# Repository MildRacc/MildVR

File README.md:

# MildVR

MildVR is a completely open-source VR headset with Windows, Linux, and macOS support in mind front the get-go. The goal of this project is to move away from the closed ecosystems of major VR companies like Meta. With the Quest lineup, Meta forces users to make accounts and limits PCVR usage to Windows by keeping their runtime proprietary. That means anyone using macOS or Linux is locked out completely. MildVR is different. It will use the open-source Monado runtime, which works across all three major desktop operating systems. It will never require and account, sign-in, or any proprietary software to function. Every part of the project, from the headset hardware, to the controllers, to the source code, will all be open for anyone to study, modify, or improve. My ultimate goal is to create a VR headset that anyone can build, understand, and use freely without being tied to any company, operating system, or proprietary software.

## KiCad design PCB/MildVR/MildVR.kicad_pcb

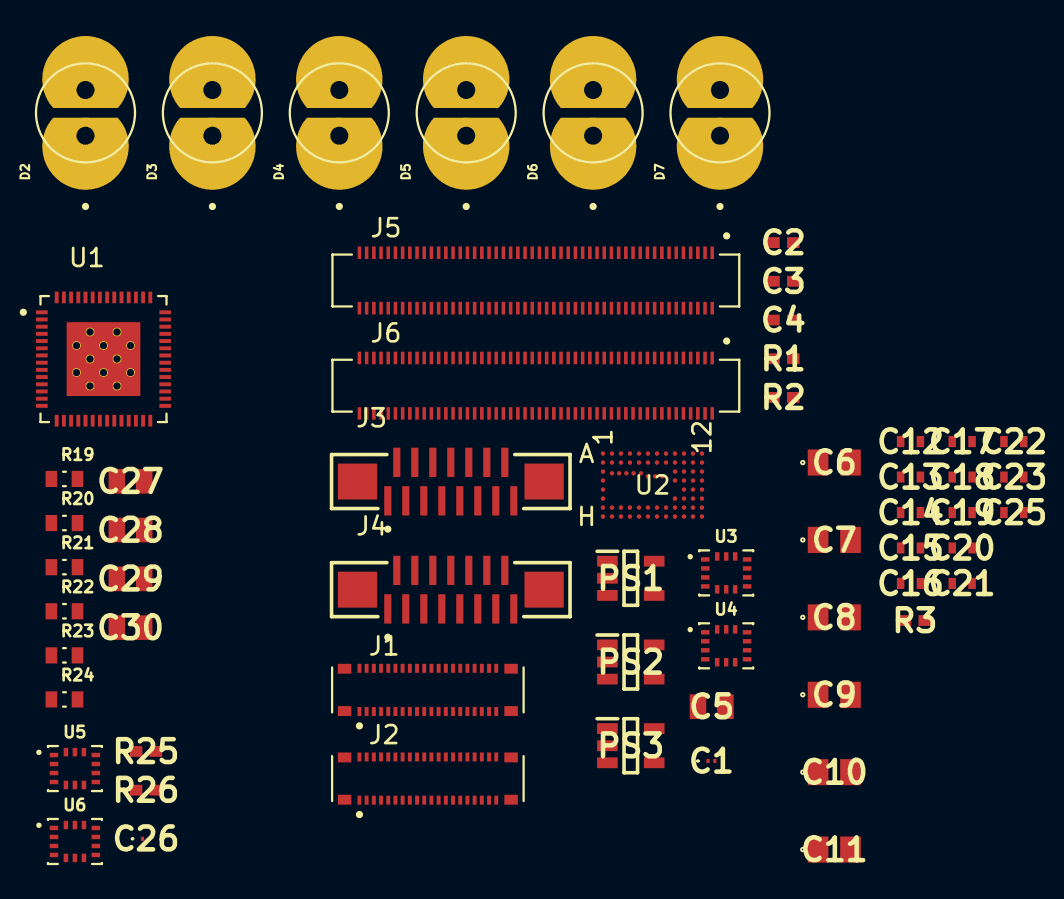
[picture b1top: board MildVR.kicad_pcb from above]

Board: 2 copper layers, 61 parts (0 on the bottom side), 41 nets, no tracks yet.

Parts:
C1, C26: 10nF; GRM022C81C222KE01L
C2, C3, C4: 100nF; RESC1005X40N
C5, C27, C28, C29, C30: 100nF; CAPC2012X94L
C6, C7, C8, C9, C10, C11: 1uF; C0805
C12, C13, C14, C15, C16, C17, C18, C19, C20, C21, C22: 1nF; CAPC1005X55N
C23, C25: 100nF; CAPC1005X55N
D2, D3, D4, D5, D6, D7: LED; DIO_SFH_4556
J1, J2: WP7B-S040VA1-R6000; (DSI) WP7B-S040VA1-R6000
J3: CAM1; SAMTEC_ZF5S-15-03-T-WT
J4: CAM2; SAMTEC_ZF5S-15-03-T-WT
J5: GPIO; HIROSE_DF40C-100DS-0.4V_51_
J6: High Speed Serial; HIROSE_DF40C-100DS-0.4V_51_
PS1, PS2, PS3: AP7365-WG-7
R1, R2, R3, R25, R26: 4.7k; RESC1005X40N
R19, R20, R21, R22, R23, R24: 16; RES_ERJU03J160V
U1: ESP32-S3
U2: HMC6301BG46
U3, U4, U5, U6: BMI270

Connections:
1.2V: C11.2 (-), PS3.5 (OUT)
1.35V: C9.2 (-), C12.2 (-), C13.1 (+), C14.2 (-), C15.1 (+), C16.1 (+), C17.2 (-), C18.2 (-), C19.2 (-), PS2.5 (OUT), U2.A9 (VCCDIV), U2.A10 (VCCDIV), U2.A11 (VCCDIV), U2.A12 (VCCDIV), U2.B5 (VDDD), U2.B10 (VCCDIV), U2.B11 (VCCDIV), U2.B12 (VCCDIV), U2.C9 (VSSDIV), U2.C10 (VSSDIV), U2.C11 (VSSDIV), U2.C12 (VSSDIV), U2.F9 (VDDSYN), U2.G3 (VCCMIX), U2.G5 (VCCTRIP), U2.G7 (VSSVCO), U2.G8 (VSSVCO), U2.G9 (VCCVCO), U2.G10 (VCCVCO), U2.G12 (VDDSYN), U2.H2 (VCOLNA), U2.H3 (VCCIF), U2.H6 (VSSVCO), U2.H9 (VSSVCO), U2.H10 (VSSVCO), U2.H11 (VSSVCO), U2.H12 (VSSVCO)
2.7V: C7.2 (-), C20.1 (+), PS1.5 (OUT), R3.2 (-), U2.A5 (VCCBUF)
/1V8: J5.88, J5.90
/3V3: C1.2 (-), C2.1 (+), C3.2 (-), C4.1 (+), C5.1 (+), C6.2 (-), C8.2 (-), C10.2 (-), J3.15, J4.15, J5.84, J5.86, PS1.1 (IN), PS1.3 (EN), PS2.1 (IN), PS2.3 (EN), PS3.1 (IN), PS3.3 (EN), R1.1 (+), R2.1 (+), U3.1 (SDO), U3.5 (VDDIO), U3.8 (VDD), U3.12 (CSB), U4.5 (VDDIO), U4.8 (VDD), U4.12 (CSB)
/5V: J5.77, J5.79, J5.81, J5.83, J5.85, J5.87
/CAM0_C_P: J3.09, J6.42
/CAM0_D0_N: J3.02, J6.28
/CAM0_D0_P: J3.03, J6.30
/CAM0_D1_N: J3.05, J6.34
/CAM0_D1_P: J3.06, J3.08, J6.36
/CAM1_C_P: J4.06, J4.08, J4.09, J6.29
/CAM1_D0_N: J4.02, J6.15
/CAM1_D0_P: J4.03, J6.17
/CAM1_D1_N: J4.05, J6.21
/CAM_GPIO: J3.11, J4.11, J5.97
/CLK: J5.56, R1.2 (-), U3.13 (SCX), U4.13 (SCX)
/Right Controler/3V3: C26.2 (-), C27.1 (+), C28.1 (+), C29.1 (+), C30.2 (-), R19.2, R20.2, R21.2, R22.2, R23.2, R24.2, R25.1 (+), R26.1 (+), U1.2 (VDD3P3), U1.3 (VDD3P3), U5.1 (SDO), U5.5 (VDDIO), U5.8 (VDD), U5.12 (CSB), U6.5 (VDDIO), U6.8 (VDD), U6.12 (CSB)
/Right Controler/CLK: R26.2 (-), U5.13 (SCX), U6.13 (SCX)
/Right Controler/SDA: R25.2 (-), U5.14 (SDX), U6.14 (SDX)
/SCL0: J3.13, J5.80
/SDA: J5.58, R2.2 (-), U3.14 (SDX), U4.14 (SDX)
/SDA0: J3.14, J5.82
GND: C1.1 (+), C2.2 (-), C3.1 (+), C4.2 (-), C5.2 (-), C6.1 (+), C7.1 (+), C8.1 (+), C9.1 (+), C10.1 (+), C11.1 (+), C12.1 (+), C13.2 (-), C14.1 (+), C15.2 (-), C16.2 (-), C17.1 (+), C18.1 (+), C19.1 (+), C20.2 (-), C23.2 (-), C25.1 (+), J3.01, J3.04, J3.07, J3.10, J4.01, J4.04, J4.07, J4.10, J5.1, J5.2, J5.7, J5.8, J5.13, J5.14, J5.22, J5.23, J5.32, J5.33, J5.42, J5.43, J5.52, J5.53, J5.59, J5.60, J5.65, J5.66, J5.71, J5.74, J5.98, J6.7, J6.8, J6.13, J6.14, J6.19, J6.20, J6.25, J6.26, J6.31, J6.32, J6.37, J6.38, J6.44, J6.50, J6.55, J6.56, J6.61, J6.62, J6.67, J6.68, J6.73, J6.74, J6.79, J6.80, J6.85, J6.86, J6.91, J6.92, J6.97, J6.98, PS1.2 (GND), PS2.2 (GND), PS3.2 (GND), U2.B3 (GND), U2.B4 (GND), U2.B6 (GND), U2.B7 (GND), U2.C1 (GND), U2.C2 (GND), U2.C3 (GND), U2.C4 (GND), U2.C5 (GND), U2.C6 (GND), U2.D1 (GND), U2.D6 (GND), U2.D7 (GND), U2.D8 (GND), U2.F1 (GND), U2.G2 (GND), U2.G4 (GND), U2.H1 (GND), U2.H5 (GND), U3.6 (GNDIO), U3.7 (GND), U4.1 (SDO), U4.6 (GNDIO), U4.7 (GND)
GND1: C26.1 (+), C27.2 (-), C28.2 (-), C29.2 (-), C30.1 (+), D2.1 (K), D3.1 (K), D4.1 (K), D5.1 (K), D6.1 (K), D7.1 (K), U1.57 (GND), U5.6 (GNDIO), U5.7 (GND), U6.1 (SDO), U6.6 (GNDIO), U6.7 (GND)
unnamed: C21.1 (+), U2.B9 (EXTFIL_N)
unnamed: C21.2 (-), U2.B8 (EXTFIL_P)
unnamed: C23.1 (+), U2.G11 (VCCRCAP)
unnamed: C25.2 (-), U2.G6 (VREGOUT)
unnamed: D2.2 (A), R24.1
unnamed: D3.2 (A), R23.1
unnamed: D4.2 (A), R22.1
unnamed: D5.2 (A), R21.1
unnamed: D6.2 (A), R19.1
unnamed: D7.2 (A), R20.1
unnamed: J1.S1 (SHIELD), J1.S2 (SHIELD), J1.S3 (SHIELD), J1.S4 (SHIELD)
unnamed: J2.S1 (SHIELD), J2.S2 (SHIELD), J2.S3 (SHIELD), J2.S4 (SHIELD)
unnamed: PS1.4 (ADJ), R3.1 (+)
unnamed: U2.E10 (VSSCP), U2.E11 (VSSCP)
unnamed: U2.D9 (VSSLPF), U2.D10 (VSSLPF), U2.D11 (VSSLPF), U2.D12 (VSSLPF)
unnamed: U2.F10 (VSSREF), U2.F11 (VSSREF)

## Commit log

2025-11-03 Create KiCad project
2025-11-03 Begin wiring of BMI270s
2025-11-19 [PCB] Routing Gyros and Receiver power
2025-11-19 Clone Blueprint desc into readme
    Will update and expand upon later, this is placeholder
2025-11-20 [PCB] Reciever Setup Routing + Organization
2025-11-22 [PCB] Replace ESP32-S3 with Raspbery Pi CM4
2025-11-23 [Firmware] init]
2025-12-30 Organization and stuff
2025-12-31 Replaced HMC6301 with M.2 PCIe Key E
2026-02-13 Replace CM4 connectors with CM3588 ones
